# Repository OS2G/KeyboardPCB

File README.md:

# KeyboardPCB
Prototype for a cellphone's keyboard

Current version is garbage, would be wise to include the original image with the key mapping to this repo.

The Super FN button is what allows the user to use the function and volume controls.

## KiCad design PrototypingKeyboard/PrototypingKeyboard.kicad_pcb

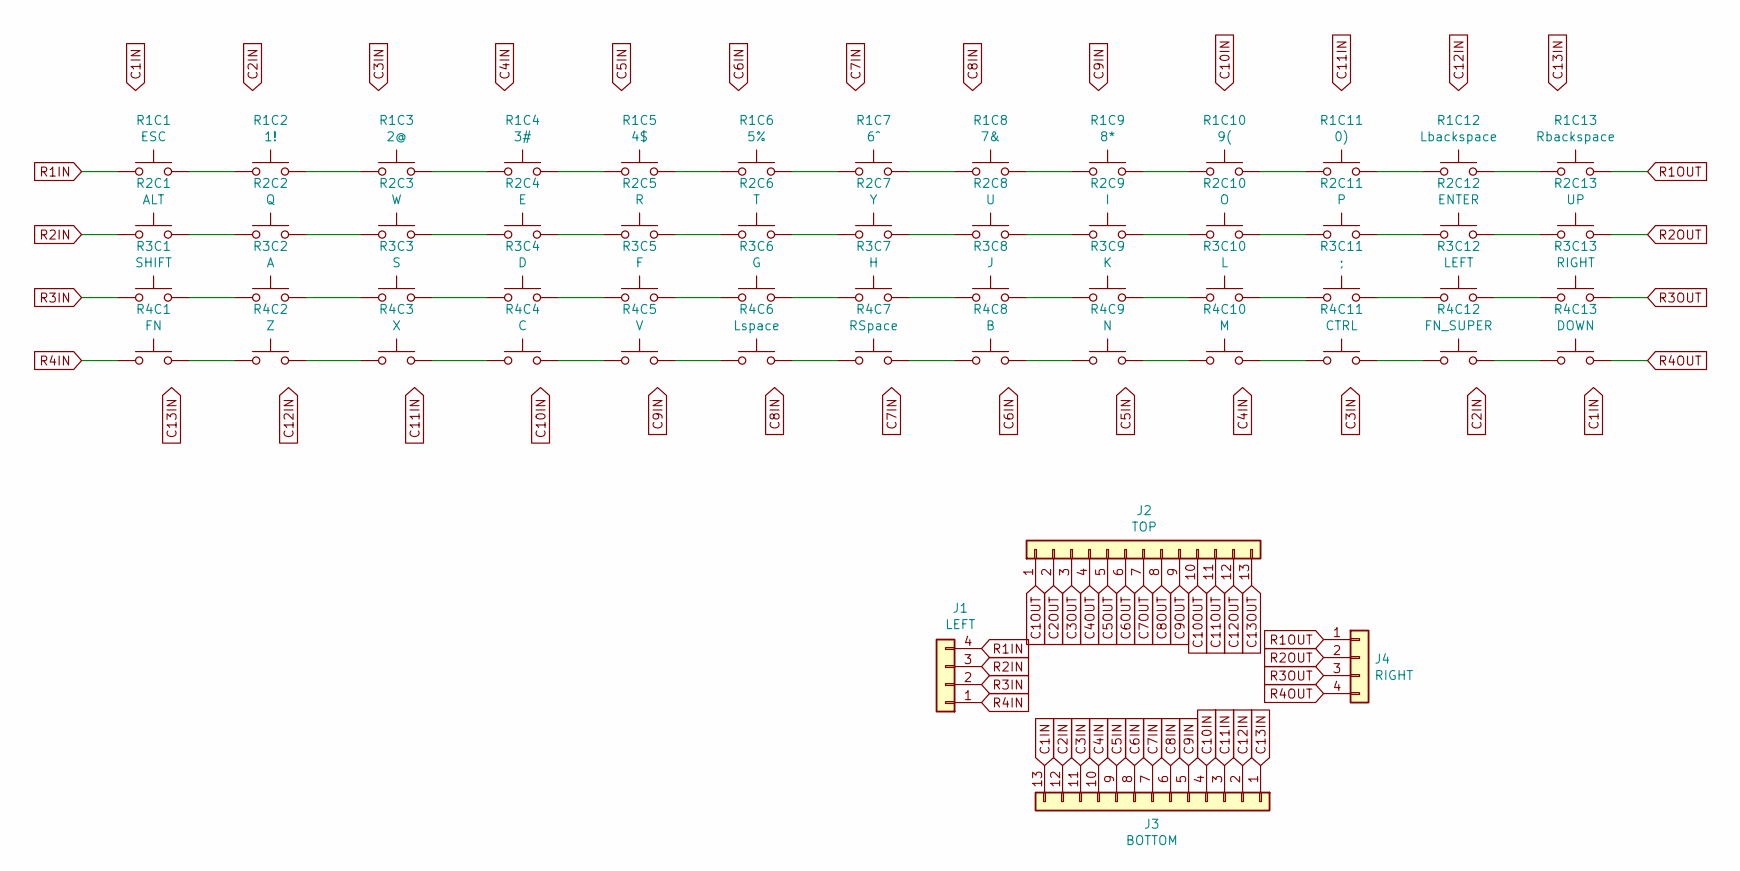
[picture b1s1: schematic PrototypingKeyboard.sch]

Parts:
J1: LEFT; PinSocket_1x04_P2.54mm_Vertical
J2: TOP; PinSocket_1x13_P2.54mm_Horizontal
J3: BOTTOM; PinSocket_1x13_P2.54mm_Horizontal
J4: RIGHT; PinSocket_1x04_P2.54mm_Vertical
R1C1: ESC; SW_SPST_EVPBF
R1C2: 1!; SW_SPST_EVPBF
R1C3: 2@; SW_SPST_EVPBF
R1C4: 3#; SW_SPST_EVPBF
R1C5: 4$; SW_SPST_EVPBF
R1C6: 5%; SW_SPST_EVPBF
R1C7: 6^; SW_SPST_EVPBF
R1C8: 7&; SW_SPST_EVPBF
R1C9: 8*; SW_SPST_EVPBF
R1C10: 9(; SW_SPST_EVPBF
R1C11: 0); SW_SPST_EVPBF
R1C12: Lbackspace; SW_SPST_EVPBF
R1C13: Rbackspace; SW_SPST_EVPBF
R2C1: ALT; SW_SPST_EVPBF
R2C2: Q; SW_SPST_EVPBF
R2C3: W; SW_SPST_EVPBF
R2C4: E; SW_SPST_EVPBF
R2C5: R; SW_SPST_EVPBF
R2C6: T; SW_SPST_EVPBF
R2C7: Y; SW_SPST_EVPBF
R2C8: U; SW_SPST_EVPBF
R2C9: I; SW_SPST_EVPBF
R2C10: O; SW_SPST_EVPBF
R2C11: P; SW_SPST_EVPBF
R2C12: ENTER; SW_SPST_EVPBF
R2C13: UP; SW_SPST_EVPBF
R3C1: SHIFT; SW_SPST_EVPBF
R3C2: A; SW_SPST_EVPBF
R3C3: S; SW_SPST_EVPBF
R3C4: D; SW_SPST_EVPBF
R3C5: F; SW_SPST_EVPBF
R3C6: G; SW_SPST_EVPBF
R3C7: H; SW_SPST_EVPBF
R3C8: J; SW_SPST_EVPBF
R3C9: K; SW_SPST_EVPBF
R3C10: L; SW_SPST_EVPBF
R3C11: ;; SW_SPST_EVPBF
R3C12: LEFT; SW_SPST_EVPBF
R3C13: RIGHT; SW_SPST_EVPBF
R4C1: FN; SW_SPST_EVPBF
R4C2: Z; SW_SPST_EVPBF
R4C3: X; SW_SPST_EVPBF
R4C4: C; SW_SPST_EVPBF
R4C5: V; SW_SPST_EVPBF
R4C6: Lspace; SW_SPST_EVPBF
R4C7: RSpace; SW_SPST_EVPBF
R4C8: B; SW_SPST_EVPBF
R4C9: N; SW_SPST_EVPBF
R4C10: M; SW_SPST_EVPBF
R4C11: CTRL; SW_SPST_EVPBF
R4C12: FN_SUPER; SW_SPST_EVPBF
R4C13: DOWN; SW_SPST_EVPBF

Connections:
C1IN: J3.13
C1OUT: J2.1
C2IN: J3.12
C2OUT: J2.2
C3IN: J3.11
C3OUT: J2.3
C4IN: J3.10
C4OUT: J2.4
C5IN: J3.9
C5OUT: J2.5
C6IN: J3.8
C6OUT: J2.6
C7IN: J3.7
C7OUT: J2.7
C8IN: J3.6
C8OUT: J2.8
C9IN: J3.5
C9OUT: J2.9
C10IN: J3.4
C10OUT: J2.10
C11IN: J3.3
C11OUT: J2.11
C12IN: J3.2
C12OUT: J2.12
C13IN: J3.1
C13OUT: J2.13
unnamed: R1C1.2, R1C2.1
unnamed: R1C2.2, R1C3.1
unnamed: R1C3.2, R1C4.1
unnamed: R1C4.2, R1C5.1
unnamed: R1C5.2, R1C6.1
unnamed: R1C6.2, R1C7.1
unnamed: R1C7.2, R1C8.1
unnamed: R1C8.2, R1C9.1
unnamed: R1C9.2, R1C10.1
unnamed: R1C10.2, R1C11.1
unnamed: R1C11.2, R1C12.1
unnamed: R1C12.2, R1C13.1
unnamed: R2C1.2, R2C2.1
unnamed: R2C2.2, R2C3.1
unnamed: R2C3.2, R2C4.1
unnamed: R2C4.2, R2C5.1
unnamed: R2C5.2, R2C6.1
unnamed: R2C6.2, R2C7.1
unnamed: R2C7.2, R2C8.1
unnamed: R2C8.2, R2C9.1
unnamed: R2C9.2, R2C10.1
unnamed: R2C10.2, R2C11.1
unnamed: R2C11.2, R2C12.1
unnamed: R2C12.2, R2C13.1
unnamed: R3C1.2, R3C2.1
unnamed: R3C2.2, R3C3.1
unnamed: R3C3.2, R3C4.1
unnamed: R3C4.2, R3C5.1
unnamed: R3C5.2, R3C6.1
unnamed: R3C6.2, R3C7.1
unnamed: R3C7.2, R3C8.1
unnamed: R3C8.2, R3C9.1
unnamed: R3C9.2, R3C10.1
unnamed: R3C10.2, R3C11.1
unnamed: R3C11.2, R3C12.1
unnamed: R3C12.2, R3C13.1
unnamed: R4C1.2, R4C2.1
unnamed: R4C2.2, R4C3.1
unnamed: R4C3.2, R4C4.1
unnamed: R4C4.2, R4C5.1
unnamed: R4C5.2, R4C6.1
unnamed: R4C6.2, R4C7.1
unnamed: R4C7.2, R4C8.1
unnamed: R4C8.2, R4C9.1
unnamed: R4C9.2, R4C10.1
unnamed: R4C10.2, R4C11.1
unnamed: R4C11.2, R4C12.1
unnamed: R4C12.2, R4C13.1
R1IN: J1.4, R1C1.1
R1OUT: J4.1, R1C13.2
R2IN: J1.3, R2C1.1
R2OUT: J4.2, R2C13.2
R3IN: J1.2, R3C1.1
R3OUT: J4.3, R3C13.2
R4IN: J1.1, R4C1.1
R4OUT: J4.4, R4C13.2

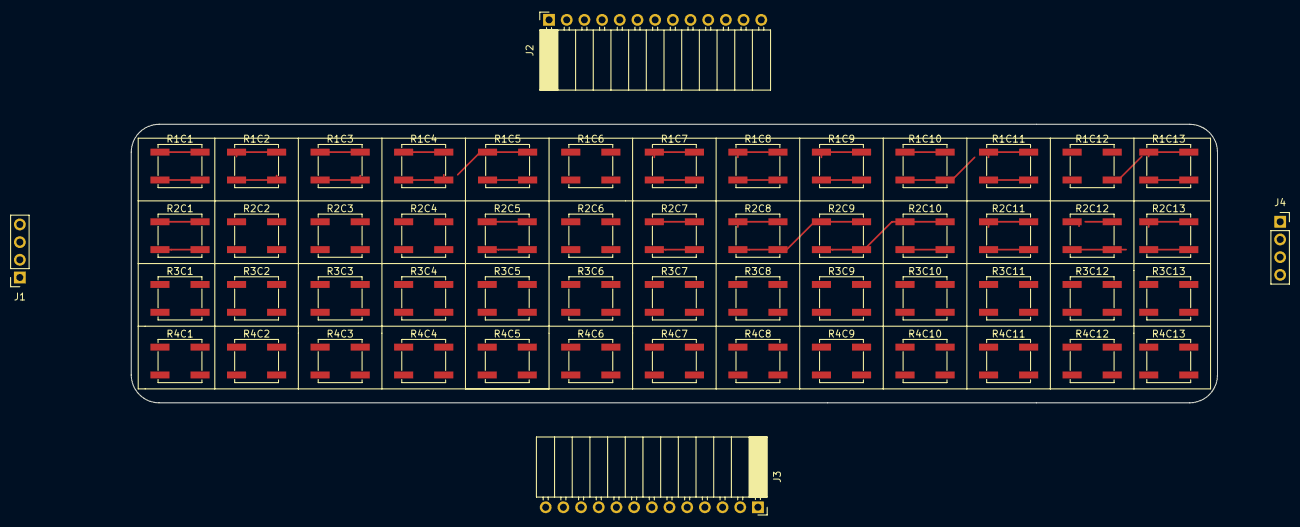
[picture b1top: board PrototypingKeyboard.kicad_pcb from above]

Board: 2 copper layers, 156.0 x 40.0 mm, 56 parts (0 on the bottom side), 56 nets.

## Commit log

2020-09-07 Update README.md
    Basic details
2020-09-07 so help me if the f***ing line endings get screwed up somewhere in the mix doing this
2020-09-07 Fixed typo in readme
2020-09-14 pictures for the lazy
